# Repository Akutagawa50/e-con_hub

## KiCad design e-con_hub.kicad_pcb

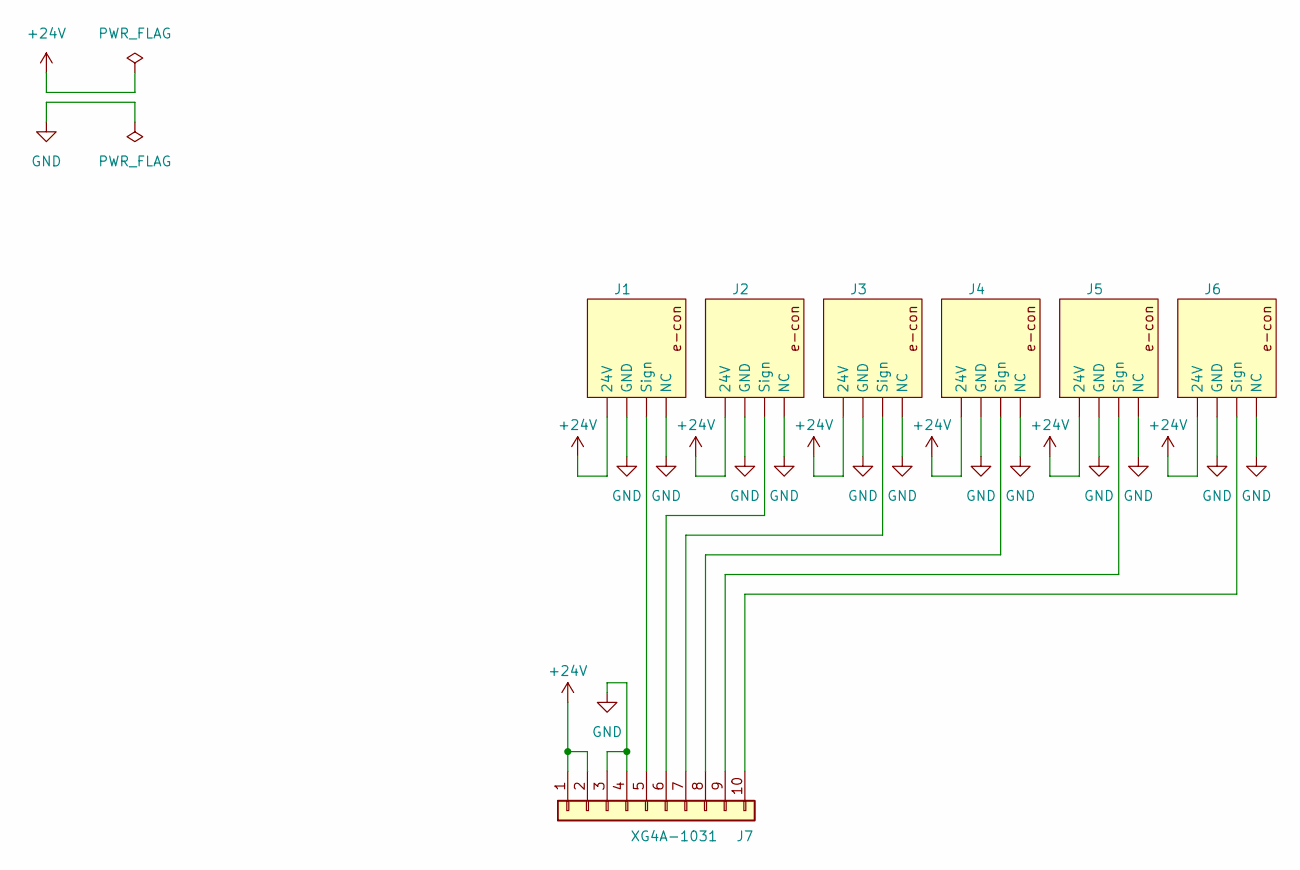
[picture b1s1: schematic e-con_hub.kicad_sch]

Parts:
J1, J2, J3, J4, J5, J6: XN2D-1371
J7: XG4A-1031; PinHeader_2x05_P2.54mm_Vertical

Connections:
+24V: J1.24V, J2.24V, J3.24V, J4.24V, J5.24V, J6.24V, J7.1, J7.2
GND: J1.GND, J1.NC, J2.GND, J2.NC, J3.GND, J3.NC, J4.GND, J4.NC, J5.GND, J5.NC, J6.GND, J6.NC, J7.3, J7.4
unnamed: J1.Sign, J7.5
unnamed: J2.Sign, J7.6
unnamed: J3.Sign, J7.7
unnamed: J4.Sign, J7.8
unnamed: J5.Sign, J7.9
unnamed: J6.Sign, J7.10

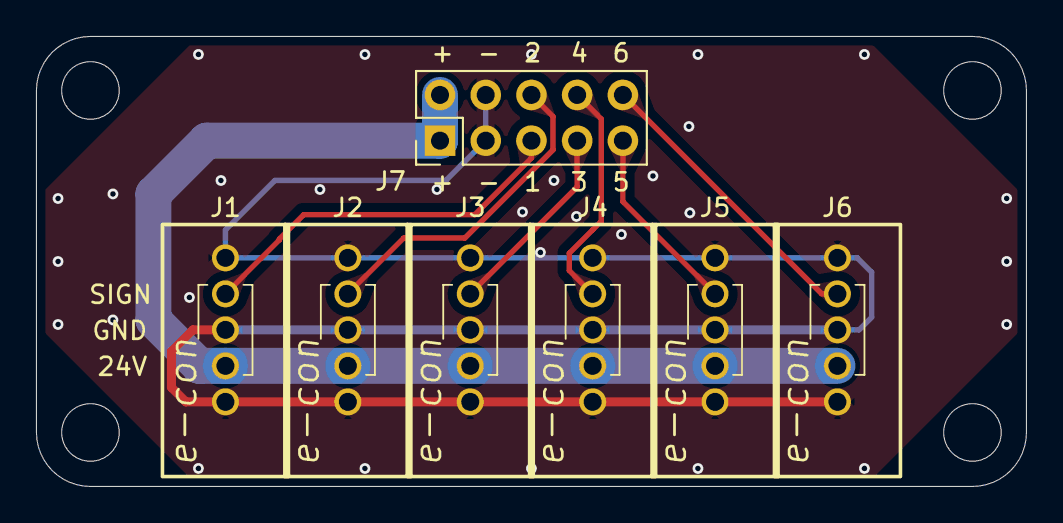
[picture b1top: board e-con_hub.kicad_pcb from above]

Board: 2 copper layers, 55.0 x 25.0 mm, 7 parts (0 on the bottom side), 8 nets.

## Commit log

2025-06-04 初コミット
2025-06-06 回路図PDFを追加
2025-06-06 パターンを微修正
2025-06-06 J7をL型milコネクタに変更
